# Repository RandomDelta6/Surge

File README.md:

# Introduction

This is a basic Passive Surge Protector PCB. It features robust large traces for high current carrying capacity and ensuring safety by preventing heating along unexpected regions. This board features an extremely small form factor of 61.6mm x 36.3mm so that it can be easily incorporated in any housing. It also features 3 M2 mounting points for securing the board to the housing. It is designed as a single sided pcb to reduce costs. Provides protection against Voltage Spikes, Short Circuit and Over Current.

Continuous Duty Electrical Rating: 250V/15A/50Hz/3750W   
Maximum Energy Dissipation: 396J    
Maximum Spike Current: 12,000 A   
Response Time: Less than 1 nanosecond
Maximum spike voltage: 6kV

Features Include :      
Thermal Resettable Fuse    
Low Cost   
Small Footprint   

# Schematic

# PCB

PCB Back View

PCB Front View

# Product Design Considerations

Proceed to place all components on the back of the board. Use 10AWG Wires for Input Cabling. Use 0.75 - 1.00 cm brass / copper strips as bus bars for the outlets. rails used for Live and Neutral supply in the Surge Protected Power Strip are expected to be soldered directly to the PCB. The brass strip should be slid in from the back side into the appropriate slit marked for it, folded down on the front side and then soldered onto the large flat pad for it. A short 10AWG wire should be soldered onto the Ground rail to the Ground Output on the PCB. Recommended for 6/8 Outlet Surge Protector Strips. Recommend Body to be made out of Thick ABS. 

The discrete Neon lamp indicates protection status, incase it is not glowing even when neon lamp in TCB is glowing, it indicates the safety circuit is blown and product needs to be replaced, as the lamp is parallel to ouput, when the lamp is not glowing, the devices connected to the strip will no longer be connected to power as well, this is in contrast to general power strips which may continue to supply power to connected devices even after safety circuit is compromised, relying on the user to notice the protection indicator is no longer lit, leaving devices vulnerable.

Thermal Fuses have a slightly higher rating of 20A as opposed to 15A of TCB, TCB has a faster action time and hence will be "resettable" after a brief period of rest when triggered. The thermal fuses act as additional protection incase of failure of TCB to cutoff power even when Current threshold is crossed. Additionally they are sandwiched between the MOVs so that the heat dissipated by MOVs incase of continuous or large Voltage Spike can cause the fuses to reach their activation temperature and blow to cut power to devices.

Dip soldering is recommended for the pcb assembly. All components should be inserted in from the back side , have excess leads trimmed and rail bars folded and then have the front side be dipped in solder bath to ensure uniform and sufficient solder coverage for efficient electrical connection.

Plastic Prongs or Screw Posts maybe provided on the frame for mounting the PCB. 3 M2 holes are provided on PCB for attaching via screws or plastic push pins. Flat Plastic Protrusions maybe used as guides for PCB placement as well as enhanced isolation, they are expected to slide into the long rectangular cutouts between L out and N out traces and N and E traces. 

# Notes

All items are mounted on the back of the board. A 23AWG wire (0 ohm link) should be run across the back of the board from Epass1 to Epass2. Solder mask is not used on either side of the board. It is not used on the front to allow for deposited solder to increase current carrying capacity. It is not used on the back since it is not required. All copper traces are on the front side of the board only as a cost saving measure. NPTH maybe used to reduce cost further. 

The Fuse and MOV Array maybe encapsulated in a piece of heatshrink tube of sufficient size.  The Brass rails used for Live and Neutral supply in the Surge Protected Power Strip are expected to be soldered directly to the PCB. The brass strip should be slid in from the back side into the appropriate slit marked for it, folded down on the front side and then soldered onto the large flat pad for it. 

Couldn't find a proper model for Thermal Circuit Breaker, so it is missing in PCB view.

This project was made with Kicad 7.0 . Updated on Kicad 8.0.3   
Generate gerbers as per specifications of the fab of your choice.

# Disclaimer
This board has not been printed and tested physically to verify functionality. I do not assume any liability for the materials, information and opinions provided on, or available through, this project. I disclaim any liability for injury, death or damages resulting from the use thereof. Modify or work on it at your own risk.

# Licensing
All PCB design files and hardware are released under the [Creative Commons Attribution Share Alike 4.0 license](https://choosealicense.com/licenses/cc-by-sa-4.0/). 

Commercial Usage strictly disallowed.

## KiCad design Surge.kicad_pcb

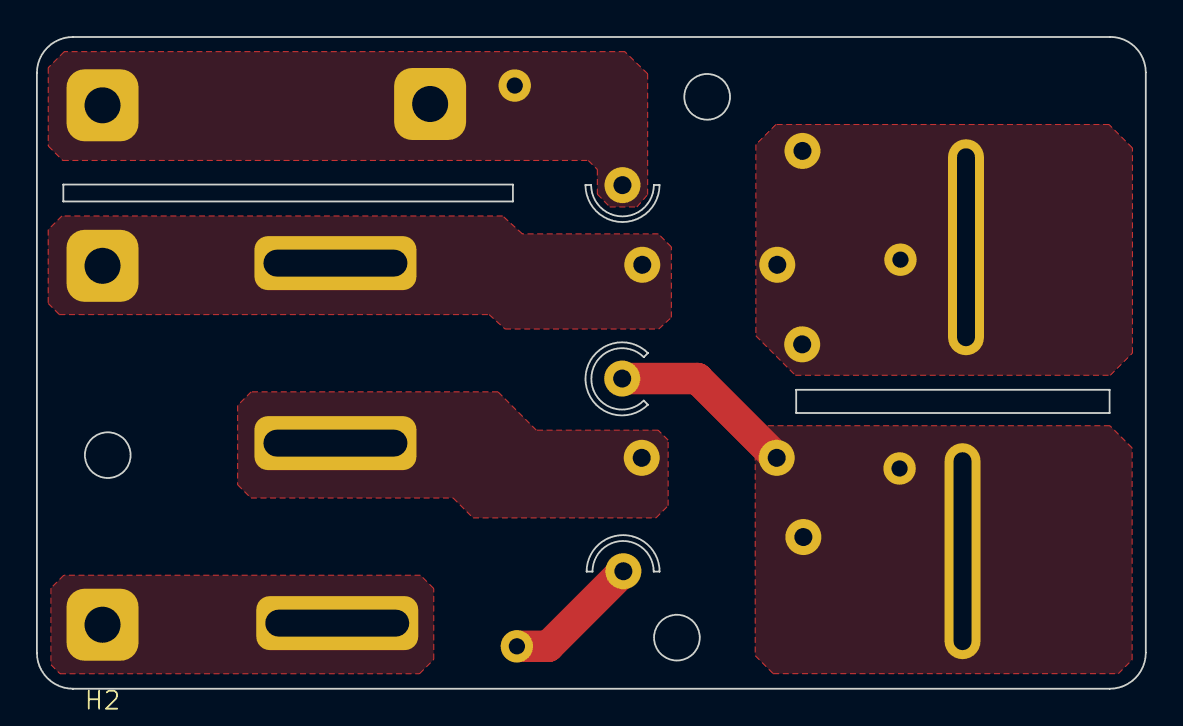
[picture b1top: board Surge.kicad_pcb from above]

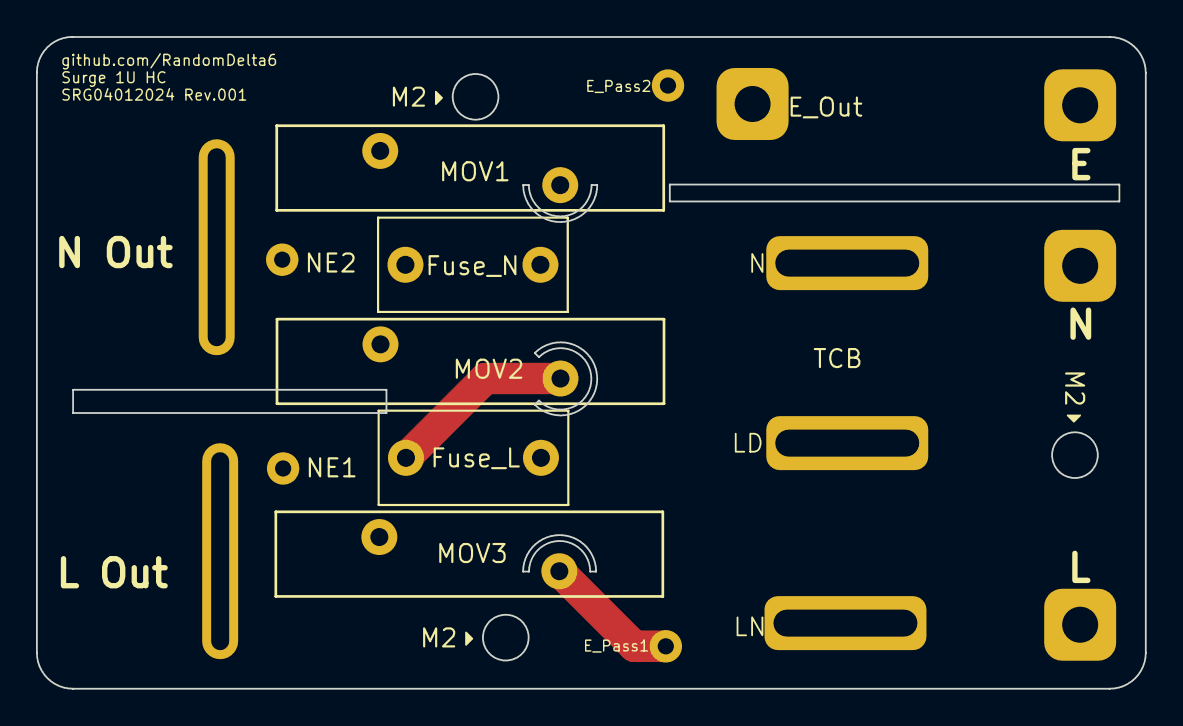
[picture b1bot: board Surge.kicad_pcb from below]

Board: 2 copper layers, 61.6 x 36.2 mm, 16 parts (6 on the bottom side), 7 nets.

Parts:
F1, F2: TCO 115C 20A 250V; C_Rect_L10.3mm_W5.0mm_P7.50mm_MKS4
H1: N_in; I_Hole
H2: L_in; I_Hole
H3: E_in; I_Hole
H4: N_out; L_Hole
H5: L_out; L_Hole
H6: E_out; I_Hole
J1, J2: NEmount
NE1: NE_N; NEmount
NE2: NE_L; NEmount
RV1, RV2, RV3: 471K; RV_Disc_D21.5mm_W4.7mm_P10mm
SW1: C1005B 15A TCB; Switch

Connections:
Earth: H3.1, H6.1, J2.1, RV1.2
unnamed: F1.1, H4.1, NE1.1, RV1.1, RV2.1
unnamed: F2.1, H5.1, NE2.1, RV2.2, RV3.1
unnamed: J1.1, RV3.2
unnamed: H2.1, SW1.3 (Line)
unnamed: F2.2, SW1.2 (Load)
unnamed: F1.2, H1.1, SW1.1 (N)

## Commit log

2023-12-20 Create LICENSE
2023-12-21 update values
2023-12-22 Updated Footprints
2023-12-23 update footprints
2024-01-03 Updated board layout
2024-01-14 Refined Layout
2024-01-14 update layout
2024-01-19 Update Schematics
2024-07-08 Update BOM and ReadMe
